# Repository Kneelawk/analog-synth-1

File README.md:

# analog-synth-1
A simple 1v/oct synth using op-amps

This project is a version of the 1v/oct synth from [DIY Synth Series Part 1 - The Exponential VCO](https://www.allaboutcircuits.com/projects/diy-synth-series-vco/) modified to use the TL084 and to fit into a 12hp module.

In addition this module has a multicolor LED that lights depending on the CV and GATE values.

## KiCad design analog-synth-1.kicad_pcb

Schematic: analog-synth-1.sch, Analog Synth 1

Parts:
C1, C2, C3, C4, C6, C7, C8, C10, C11, C15: 100nf; C_Disc_D5.0mm_W2.5mm_P2.50mm
C5: 1nf; C_Disc_D3.8mm_W2.6mm_P2.50mm
C9: 4nf; C_Rect_L7.0mm_W3.5mm_P2.50mm_P5.00mm
C12, C13, C14: 100uf; CP_Radial_D6.3mm_P2.50mm
J1: CONN_02X08; Pin_Header_Straight_2x08_Pitch2.54mm
J2, J3, J4, J5: PJ301M-12
Q1, Q2, Q3, Q5, Q6: 2N3904; TO-92_Inline_Wide
Q4: 2N3906; TO-92_Inline_Wide
R1: 1M; R_Axial_DIN0207_L6.3mm_D2.5mm_P10.16mm_Horizontal
R2, R3, R8, R9, R14, R15, R16, R17: 100k; R_Axial_DIN0207_L6.3mm_D2.5mm_P10.16mm_Horizontal
R4, R18: 10k; R_Axial_DIN0207_L6.3mm_D2.5mm_P10.16mm_Horizontal
R5, R7: 1k; R_Axial_DIN0207_L6.3mm_D2.5mm_P10.16mm_Horizontal
R10, R11, R12, R13: 50k; R_Axial_DIN0207_L6.3mm_D2.5mm_P10.16mm_Horizontal
RV1, RV3, RV4: 10k; Potentiometer_Trimmer_Bourns_3296Y
RV2: 100k; Potentiometer_Trimmer_Bourns_3296Y
RV5: 10k; Potentiometer_Alps_RK09L_Sleve_Single_Horizontal_Custom
U1, U2, U3, U4, U5, U6, U7: LM741; DIP-8_W7.62mm

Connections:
+5V: C8.2, C10.1, C11.2, C13.1, C15.1, J1.11, J1.12, R1.1, R8.2, R17.1, RV5.3, U4.7, U5.7, U6.7, U7.7
+12V: C1.2, C3.2, C6.2, C12.1, J1.9, J1.10, RV3.3, U1.7, U2.7, U3.7
-12VA: C2.1, C4.1, C7.1, C14.2, J1.1, J1.2, U1.4, U2.4, U3.4
CV: J1.13, J1.14, R2.2
CV1: J2.3, R3.2
Exp-CV: RV2.1, RV4.3, U2.6
GND: C1.1, C2.2, C3.1, C4.2, C6.1, C7.2, C8.1, C10.2, C11.1, C12.2, C13.2, C14.1, C15.2, J1.3, J1.4, J1.5, J1.6, J1.7, J1.8, J2.1, J3.1, J4.1, J5.1, Q2.2 (B), Q3.1 (E), Q5.1 (E), Q6.1 (E), R12.2, R14.2, RV3.1, RV5.1, U1.3, U2.3, U3.3, U4.4, U5.4, U6.4, U7.4
Gate: J1.15, J1.16, R18.1
Gate1: J5.3, R4.2
unnamed: C5.1, R5.2, U3.6
unnamed: C5.2, Q1.3 (C), R1.2, U3.2
unnamed: C9.2, R9.1, R13.1, U5.2
unnamed: J2.2, RV5.2
unnamed: Q1.1 (E), Q2.1 (E), R5.1
unnamed: Q2.3 (C), RV2.2, RV2.3, U2.2
unnamed: Q3.2 (B), Q4.3 (C)
unnamed: Q3.3 (C), R13.2
unnamed: Q4.1 (E), R16.2
unnamed: Q4.2 (B), Q5.3 (C), Q6.3 (C), R17.2
unnamed: Q5.2 (B), R18.2
unnamed: Q6.2 (B), R4.1
unnamed: R2.1, R3.1, RV1.3, U1.2
unnamed: R7.1, RV3.2
unnamed: R7.2, RV4.1
unnamed: R10.1, R12.1, U5.3
unnamed: R9.2, R10.2, RV4.2
unnamed: R11.1, R15.2, U6.3
unnamed: R8.1, R11.2, R14.1
Sqr-SMPL: R15.1, R16.1, U6.6, U7.3
Square: J3.3, U7.2, U7.6
Tri-SMPL: C9.1, U4.3, U5.6, U6.2
Triangle: J4.3, U4.2, U4.6
VIN: Q1.2 (B), RV1.1, RV1.2, U1.6

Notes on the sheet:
Input Amp
Thermal Bonding
Exponential Converter
VCO
Output Buffers
C9's value has a drastic effect on the VCO's frequency.
RV1 is exponential product control. RV2 is product control. RV3 and RV4 are sum controls.
Pitch control pot.

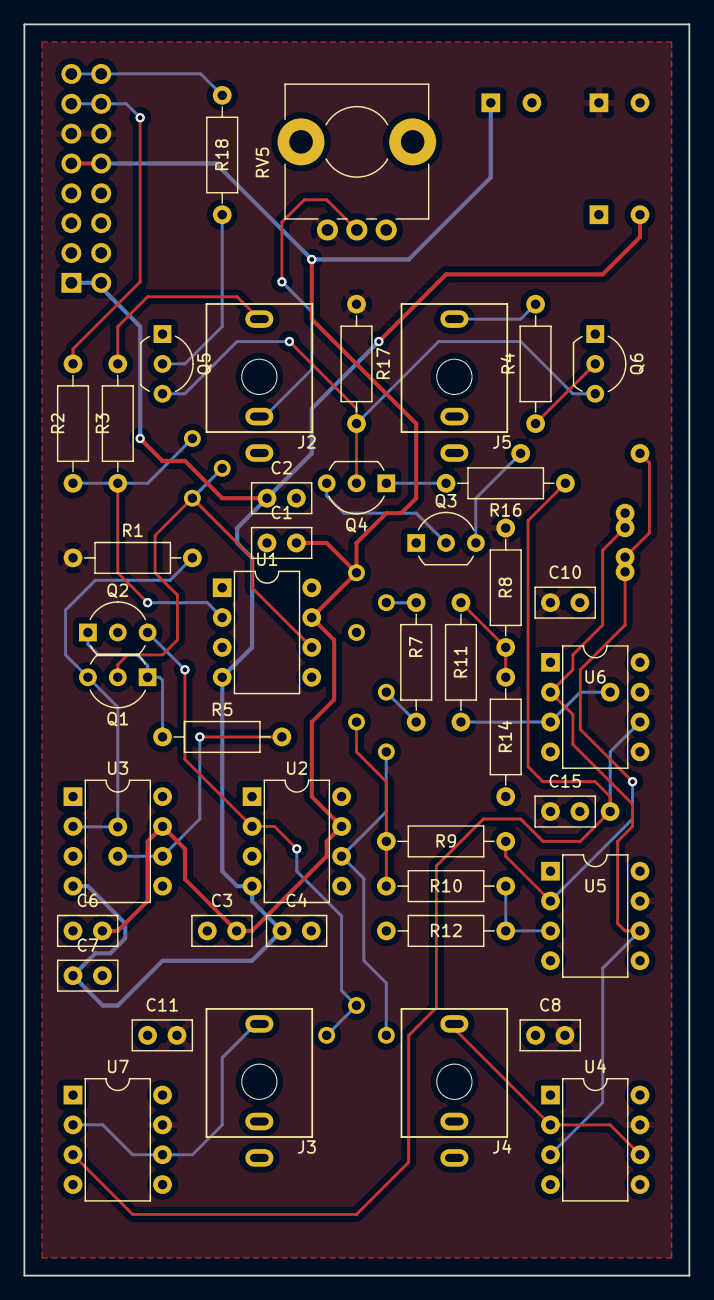
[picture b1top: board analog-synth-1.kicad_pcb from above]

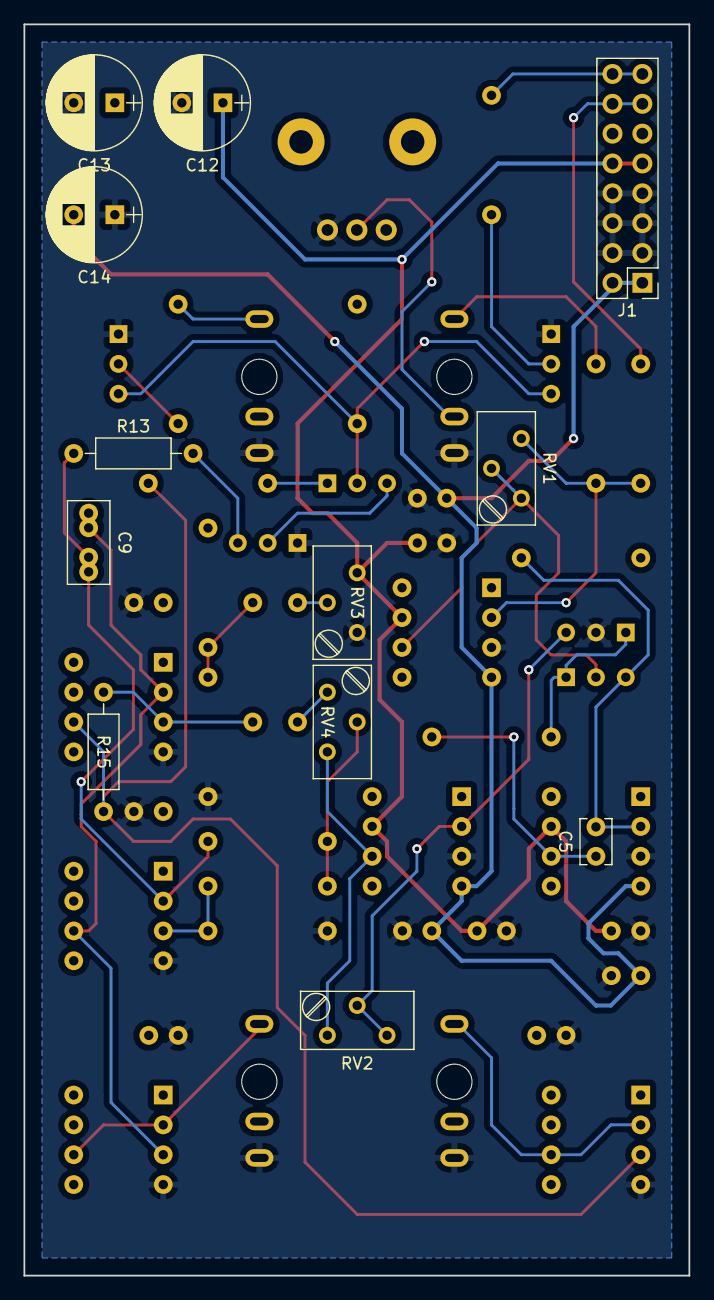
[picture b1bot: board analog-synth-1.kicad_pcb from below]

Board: 2 copper layers, 56.6 x 106.5 mm, 55 parts (12 on the bottom side), 33 nets.

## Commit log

2017-08-10 All the files rev1.0.7
2017-08-10 Change vco tuning system
2017-08-10 Move some wires around
2017-08-14 Add footprints and fix pin header orientation
2017-08-14 Change trimmer descriptions and plot pdf
2017-08-15 Use PJ301M-12 3.3mm jacks
2017-08-15 Update schematic libs, add Gate jack
2017-08-15 Use RK09L potentiometer
2017-08-17 Begin on PCB
2017-08-17 Replace 4xLM741 with LM324
2017-08-17 Finish PCB
2017-08-17 Remove conflicting files
2017-08-19 Add reference to README
2017-08-22 Add rev1.0.12 pdf
2017-08-22 Fix VCO tuning rev1.0.13
2017-08-23 Fix polarized capacitor footprints rev1.0.14
2019-03-12 Begin working on ports
2019-03-12 Add jacks
2019-03-12 Add opamp buffers
2019-03-12 Add CV input amp
2019-03-14 Finish basic synth circuit diagram
2019-03-14 Annotate components
2019-03-30 Add ATtiny85 overdrive protection, fix #5
2019-07-11 Generate plot PDF
2019-07-11 Separate synth ports and logic into different boards
2019-07-11 Re-add README.md
2019-07-11 Build port board schematics
2019-07-11 Switch from RABG to RCBG LED
2019-07-11 Replace PJ301M-12 with PJ398SM
2019-07-12 Begin on parts list
2019-07-12 Fix port board cache library
2019-07-12 Add part info for eurorack 2x8 header
2019-07-12 Add CV offset & scale system
